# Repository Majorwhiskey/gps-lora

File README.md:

# Theoros

*Theoros* (Greek θεωρός): an official observer and envoy, sent to watch
and report back.

USB-powered GPS logger with LoRa telemetry, built around the ESP32-S3.

Logs GPS fixes to a microSD card at 1 Hz, shows status on an OLED, and sends
position over 866 MHz LoRa. WiFi provides NTP time, log download and OTA
updates. Designed in KiCad as a 4-layer, fully machine-assembled board
(Lion Circuits PCBA, Bangalore, single-sided).

> **Status: V1.0 design complete** (schematic, routed PCB, fab outputs and
> firmware). Not yet fabricated or tested. Do not order boards from this
> repository until a tagged release exists.

## Features

- ESP32-S3-WROOM-1-N8 with native USB (no USB-UART bridge)
- USB-C power and data, 5 V 1 A
- u-blox SAM-M10Q GNSS module with integrated antenna, UART and PPS
- microSD logging on a dedicated SPI bus
- RFM95W (SX1276) 868 MHz-band LoRa radio on a second SPI bus, u.FL antenna
- Telemetry and SD logs encrypted and authenticated (AES-128-CCM, per-tracker
  keys); separate tracker and receiver firmware
- Bare SSD1306 128x64 OLED panel on I2C, FPC connector
- Low-dropout 3.3 V linear regulator (AP7361C)
- Tag-Connect footprint for UART0 console, EN and GPIO0
- 4-layer stackup with solid ground plane; RF and USB traces checked at about 48 and 90 ohm on Lion's standard stackup

## Block diagram

```mermaid
flowchart LR
    USB[USB-C] -->|VBUS| FUSE[Polyfuse 750 mA] --> LDO[AP7361C 3.3 V]
    USB <-->|D+ / D-| ESD[USBLC6-2] <--> MCU
    LDO -->|3V3| MCU[ESP32-S3-WROOM-1]
    MCU <-->|UART1| GPS[SAM-M10Q GNSS]
    MCU <-->|SPI2| SD[microSD]
    MCU <-->|SPI3| LORA[RFM95W 868] --> ANT[u.FL to SMA]
    MCU <-->|I2C| OLED[SSD1306 panel]
```

## Repository layout

| Path | Contents |
|---|---|
| `hardware/` | KiCad 10 project (schematic, PCB) |
| `hardware/lib/` | Project-local symbols, footprints and 3D models |
| `docs/` | Design and security specifications (Markdown and PDF), images |
| `firmware/` | ESP32-S3 firmware (Arduino, untested on hardware) |
| `production/` | Fabrication outputs (Gerbers, drill, BOM, CPL) per release |

## Documentation

- [PCB design specification](docs/PCB_DESIGN.md): pin assignment, power
  budget, layout rules and design decisions.
- [Firmware](firmware/README.md) ([PDF](docs/FIRMWARE.pdf)): tracker and
  receiver firmware, build, console, WiFi service mode, OTA, bring-up.
- [Security specification](docs/SECURITY.md) ([PDF](docs/SECURITY.pdf)):
  threat model, AES-128-CCM design, key management, LoRa packet and log
  formats, provisioning, test vectors.

PDFs are generated from the Markdown with `python3 docs/build_pdf.py`.

## Opening the design

Requires [KiCad](https://www.kicad.org/) 10.0 or later. Open
`hardware/theoros.kicad_pro`. All non-standard symbols, footprints and 3D
models are in `hardware/lib/`, so no external libraries are needed.

## Regulatory note

The LoRa radio is configured for 865–867 MHz, India's delicensed band.
Users elsewhere must set the frequency, power and duty cycle allowed in
their region.

## License

Hardware design files are licensed under the
[CERN Open Hardware Licence Version 2 – Permissive](LICENSE)
(CERN-OHL-P-2.0). Firmware (`firmware/`) is licensed under the
[Apache License 2.0](firmware/LICENSE).

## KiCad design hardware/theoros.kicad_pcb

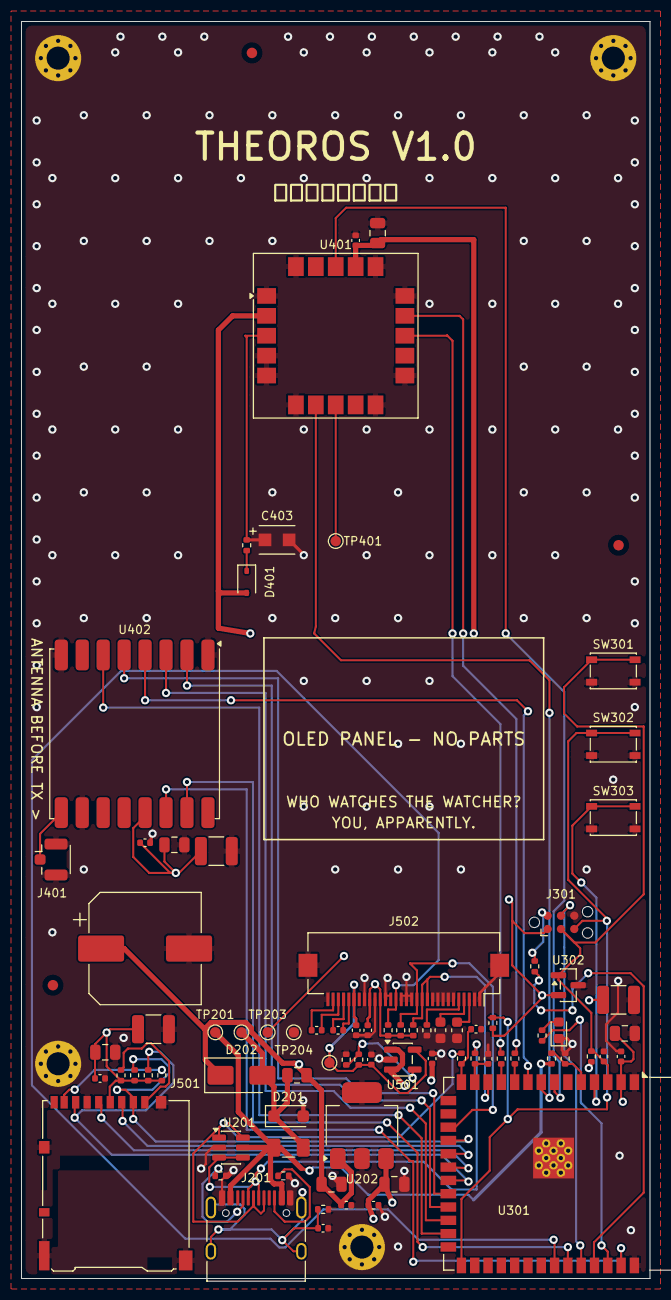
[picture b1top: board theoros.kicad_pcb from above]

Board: 4 copper layers, 60.0 x 120.0 mm, 88 parts (0 on the bottom side), 56 nets.

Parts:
C201: 4.7nF; C_0402_1005Metric
C202: 2200uF; CP_Elec_10x10.5
C203, C205: 22uF; C_0805_2012Metric
C204, C206, C303, C402, C406, C503: 100nF; C_0402_1005Metric
C301, C404, C501: 100uF; C_1210_3225Metric
C302, C401, C405, C502: 10uF; C_0805_2012Metric
C304, C504, C505, C506, C507, C510, C511: 1uF; C_0402_1005Metric
C305, C306: DNP; C_0402_1005Metric
C403: 11mF 3.3V; Seiko_CPH3225A
C508: 2.2uF; C_0603_1608Metric
C509: 4.7uF; C_0603_1608Metric
D201: SMF5.0A; D_SOD-123F
D202: Schottky; D_SMA
D301: Green; LED_0603_1608Metric
D401: BAT54; D_SOD-323
DS501: ER-OLED0.96-1.1W; OLED_ER-OLED0.96-1.1W
F201: 0.75A PTC; Fuse_1206_3216Metric
FID1, FID2, FID3: Fiducial; Fiducial_1mm_Mask2mm
H1, H2, H3, H4: MountingHole_Pad; MountingHole_2.2mm_M2_Pad_Via
J201: TYPE-C-31-M-12; USB_C_Receptacle_HRO_TYPE-C-31-M-12
J301: TC2030-NL; Tag-Connect_TC2030-IDC-NL_2x03_P1.27mm_Vertical
J401: U.FL; U.FL_Hirose_U.FL-R-SMT-1_Vertical
J501: DM3AT-SF-PEJM5; microSD_HC_Hirose_DM3AT-SF-PEJM5
J502: FH12-30S-0.5SH(55); Hirose_FH12-30S-0.5SH_1x30-1MP_P0.50mm_Horizontal
R201, R202: 5.1k; R_0402_1005Metric
R203: 1M; R_0402_1005Metric
R204: 0R; R_0805_2012Metric
R205, R301, R302, R505, R510: 10k; R_0402_1005Metric
R206: 15k; R_0402_1005Metric
R303, R401: 1k; R_0402_1005Metric
R304, R305: 0R; R_0402_1005Metric
R306: 499R; R_0402_1005Metric
R307, R308: 100R; R_0402_1005Metric
R501, R502, R503, R504: 47k; R_0402_1005Metric
R506, R507: 4.7k; R_0402_1005Metric
R508: 390k; R_0402_1005Metric
R509: 59k; R_0402_1005Metric
SW301: RESET; SW_SPST_PTS810
SW302: BOOT; SW_SPST_PTS810
SW303: EJECT; SW_SPST_PTS810
TP201, TP202, TP203, TP204: TestPoint; TestPoint_Pad_D1.0mm
TP401: SAFEBOOT; TestPoint_Pad_D1.0mm
TP501: VBAT; TestPoint_Pad_D1.0mm
U201: USBLC6-2SC6; SOT-23-6
U202: AP7361C-33E; SOT-223-3_TabPin2
U301: ESP32-S3-WROOM-1-N8; ESP32-S3-WROOM-1
U302: MCP120T-300I/TT; SOT-23
U401: SAM-M10Q; ublox_SAM-M8Q
U402: RFM95W-868S2; HOPERF_RFM9XW_SMD
U501: TLV75801PDBV; SOT-23-5

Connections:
+3V3: C205.1, C206.1, C301.1, C302.1, C303.1, C401.1, C402.1, C404.1, C405.1, C406.1, C501.1, C502.1, C503.1, C507.1, D401.2 (A), J301.1, J501.4 (VDD), J502.20, J502.22, R301.1, R302.1, R501.1, R502.1, R503.1, R504.1, R505.1, R506.1, R507.1, TP203.1 (1_1), U202.3 (VO), U301.2, U302.2 (VDD), U401.2 (VCC_IO), U401.17 (VCC), U402.13 (3.3V)
+5V: C202.1, C203.1, C204.1, C510.1, D202.1 (K), R204.2, U202.1 (VI), U501.1 (IN), U501.3 (EN)
/MCU/BOOT: J301.5, R302.2, SW302.1, U301.27
/MCU/EJECT: SW303.1, U301.4
/MCU/EN: C304.1, J301.3, R301.2, SW301.1, U301.3, U302.1 (~RST)
/MCU/IO17_TX: R307.1, U301.10
/MCU/IO18_RX: R308.1, U301.11
/MCU/IO19_DN: C306.1, R305.2, U301.13
/MCU/IO20_DP: C305.1, R304.2, U301.14
/MCU/LED: R303.1, U301.38
/MCU/LED_A: D301.2 (A), R303.2
/MCU/TXD0_R: R306.1, U301.37
/MCU/UART0_RX: J301.4, U301.36
/MCU/UART0_TX: J301.2, R306.2
/Power & USB/VBUS_FUSED: D201.1 (K), D202.2 (A), F201.2, R204.1, TP202.1 (1_1)
/Radio/GNSS_SAFEBOOT: TP401.1 (1_1), U401.8 (~SAFEBOOT)
/Radio/GNSS_VBCKP: C403.1, R401.2, U401.3 (V_BCKP)
/Radio/LORA_ANT: J401.1 (In), U402.9 (ANT)
/Storage & Display/OLED_C1N: C505.2, J502.26
/Storage & Display/OLED_C1P: C505.1, J502.27
/Storage & Display/OLED_C2N: C504.2, J502.29
/Storage & Display/OLED_C2P: C504.1, J502.28
/Storage & Display/OLED_IREF: J502.5, R508.1
/Storage & Display/OLED_VBAT: C506.1, C511.1, J502.25, R509.1, TP501.1 (1_1), U501.5 (OUT)
/Storage & Display/OLED_VCC: C508.1, J502.3
/Storage & Display/OLED_VCOMH: C509.1, J502.4
/Storage & Display/SD_DAT1: J501.8 (DAT1), R504.2
/Storage & Display/SD_DAT2: J501.1 (DAT2), R501.2
GND: C201.2, C202.2, C203.2, C204.2, C205.2, C206.2, C301.2, C302.2, C303.2, C304.2, C305.2, C306.2, C401.2, C402.2, C403.2, C404.2, C405.2, C406.2, C501.2, C502.2, C503.2, C506.2, C507.2, C508.2, C509.2, C510.2, C511.2, D201.2 (A), D301.1 (K), H1.1 (1_1), H2.1 (1_1), H3.1 (1_1), H4.1 (1_1), J201.A1 (GND), J201.A12 (GND), J201.B1 (GND), J201.B12 (GND), J301.6, J401.2 (Ext), J501.6 (VSS), J501.SH (SHIELD), J502.1, J502.2, J502.6, J502.7, J502.8, J502.9, J502.10, J502.14, J502.15, J502.16, J502.18, J502.19, J502.21, J502.23, J502.30, J502.MP (MountPin), R201.2, R202.2, R203.2, R206.2, R508.2, R510.2, SW301.2, SW302.2, SW303.2, TP204.1 (1_1), U201.2 (GND), U202.2 (GND), U301.1, U301.40, U301.41, U302.3 (VSS), U401.1 (GND), U401.4 (GND), U401.5 (GND), U401.6 (GND), U401.10 (GND), U401.11 (GND), U401.15 (GND), U401.16 (GND), U401.20 (GND), U402.1 (GND), U402.8 (GND), U402.10 (GND), U501.2 (GND)
GNSS_PPS: U301.8, U401.7 (TIMEPULSE)
GNSS_RESET_N: U301.7, U401.18 (~RESET)
GNSS_RXD: R307.2, U401.14 (RXD)
GNSS_TXD: R308.2, U401.13 (TXD)
LORA_DIO0: U301.39, U402.14 (DIO0)
LORA_DIO1: U301.35, U402.15 (DIO1)
LORA_MISO: U301.23, U402.2 (MISO)
LORA_MOSI: U301.24, U402.3 (MOSI)
LORA_NSS: U301.22, U402.5 (NSS)
LORA_RESET: U301.25, U402.6 (RESET)
LORA_SCK: U301.9, U402.4 (SCK)
unnamed: D401.1 (K), R401.1
unnamed: J201.A5 (CC1), R201.1
unnamed: J201.B5 (CC2), R202.1
unnamed: C201.1, J201.SH (SHIELD), R203.1
unnamed: R509.2, R510.1, U501.4 (FB)
OLED_RES: J502.17, R505.2, U301.34
OLED_SCL: J502.13, R507.2, U301.17
OLED_SDA: J502.11, J502.12, R506.2, U301.12
SD_CS: J501.2 (DAT3/CD), R502.2, U301.18
SD_MISO: J501.7 (DAT0), R503.2, U301.21
SD_MOSI: J501.3 (CMD), U301.19
SD_SCK: J501.5 (CLK), U301.20
USB_DN: J201.A7 (D-), J201.B7 (D-), R305.1, U201.3 (I/O2), U201.4 (I/O2)
USB_DP: J201.A6 (D+), J201.B6 (D+), R304.1, U201.1 (I/O1), U201.6 (I/O1)
VBUS: F201.1, J201.A4 (VBUS), J201.A9 (VBUS), J201.B4 (VBUS), J201.B9 (VBUS), R205.1, TP201.1 (1_1), U201.5 (VBUS)
VBUS_SENSE: R205.2, R206.1, U301.5
